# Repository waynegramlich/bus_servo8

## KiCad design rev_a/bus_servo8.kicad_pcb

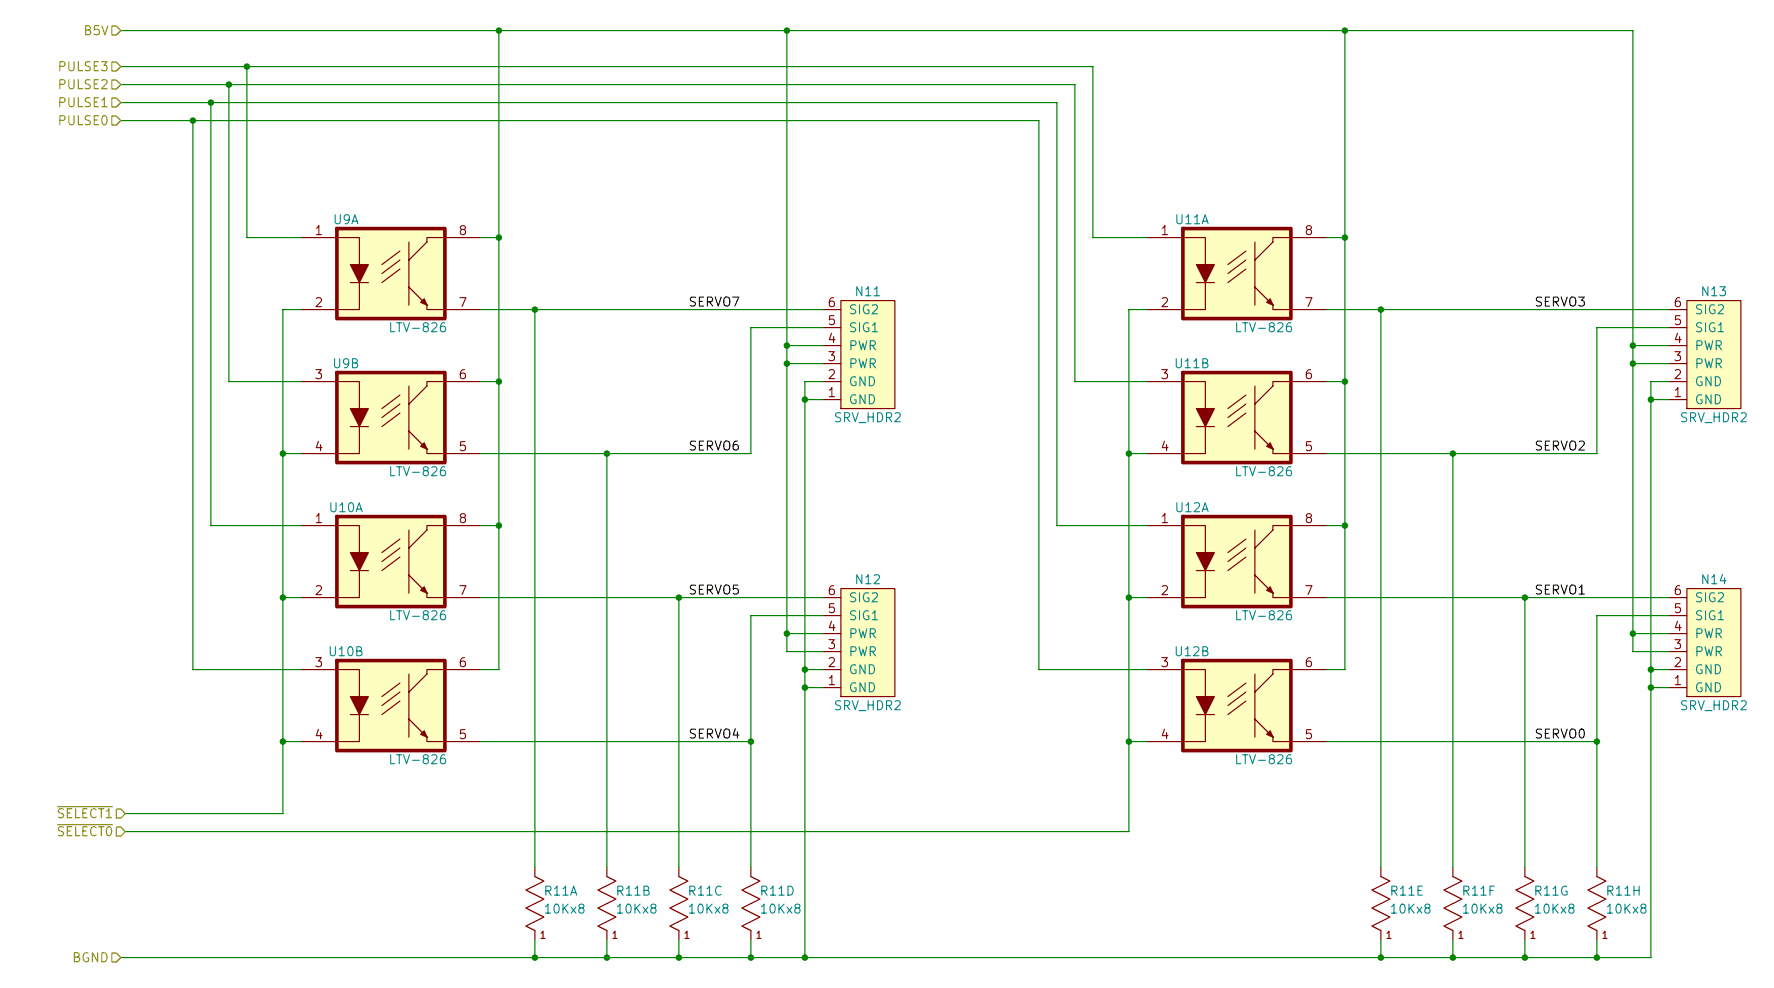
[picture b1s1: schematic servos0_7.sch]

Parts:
N11, N12, N13, N14: SRV_HDR2; Pin_Header_Straight_2x03
R11: 10Kx8; Pin_Header_Straight_1x09
U9, U10, U11, U12: LTV-826; DIP-8__300

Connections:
/Processor/B5V: N11.3 (PWR), N11.4 (PWR), N12.3 (PWR), N12.4 (PWR), N13.3 (PWR), N13.4 (PWR), N14.3 (PWR), N14.4 (PWR), U9.6, U9.8, U10.6, U10.8, U11.6, U11.8, U12.6, U12.8; also elsewhere on the board
/Processor/BGND: N11.1 (GND), N11.2 (GND), N12.1 (GND), N12.2 (GND), N13.1 (GND), N13.2 (GND), N14.1 (GND), N14.2 (GND), R11.1; also elsewhere on the board
/Processor/PULSE0: U10.3, U12.3; also elsewhere on the board
/Processor/PULSE1: U10.1, U12.1; also elsewhere on the board
/Processor/PULSE2: U9.3, U11.3; also elsewhere on the board
/Processor/PULSE3: U9.1, U11.1; also elsewhere on the board
/Processor/~SELECT0: U11.2, U11.4, U12.2, U12.4; also elsewhere on the board
/Processor/~SELECT1: U9.2, U9.4, U10.2, U10.4; also elsewhere on the board
/Servos_0:7/SERVO0: N14.5 (SIG1), R11.9, U12.5
/Servos_0:7/SERVO1: N14.6 (SIG2), R11.8, U12.7
/Servos_0:7/SERVO2: N13.5 (SIG1), R11.7, U11.5
/Servos_0:7/SERVO3: N13.6 (SIG2), R11.6, U11.7
/Servos_0:7/SERVO4: N12.5 (SIG1), R11.5, U10.5
/Servos_0:7/SERVO5: N12.6 (SIG2), R11.4, U10.7
/Servos_0:7/SERVO6: N11.5 (SIG1), R11.3, U9.5
/Servos_0:7/SERVO7: N11.6 (SIG2), R11.2, U9.7

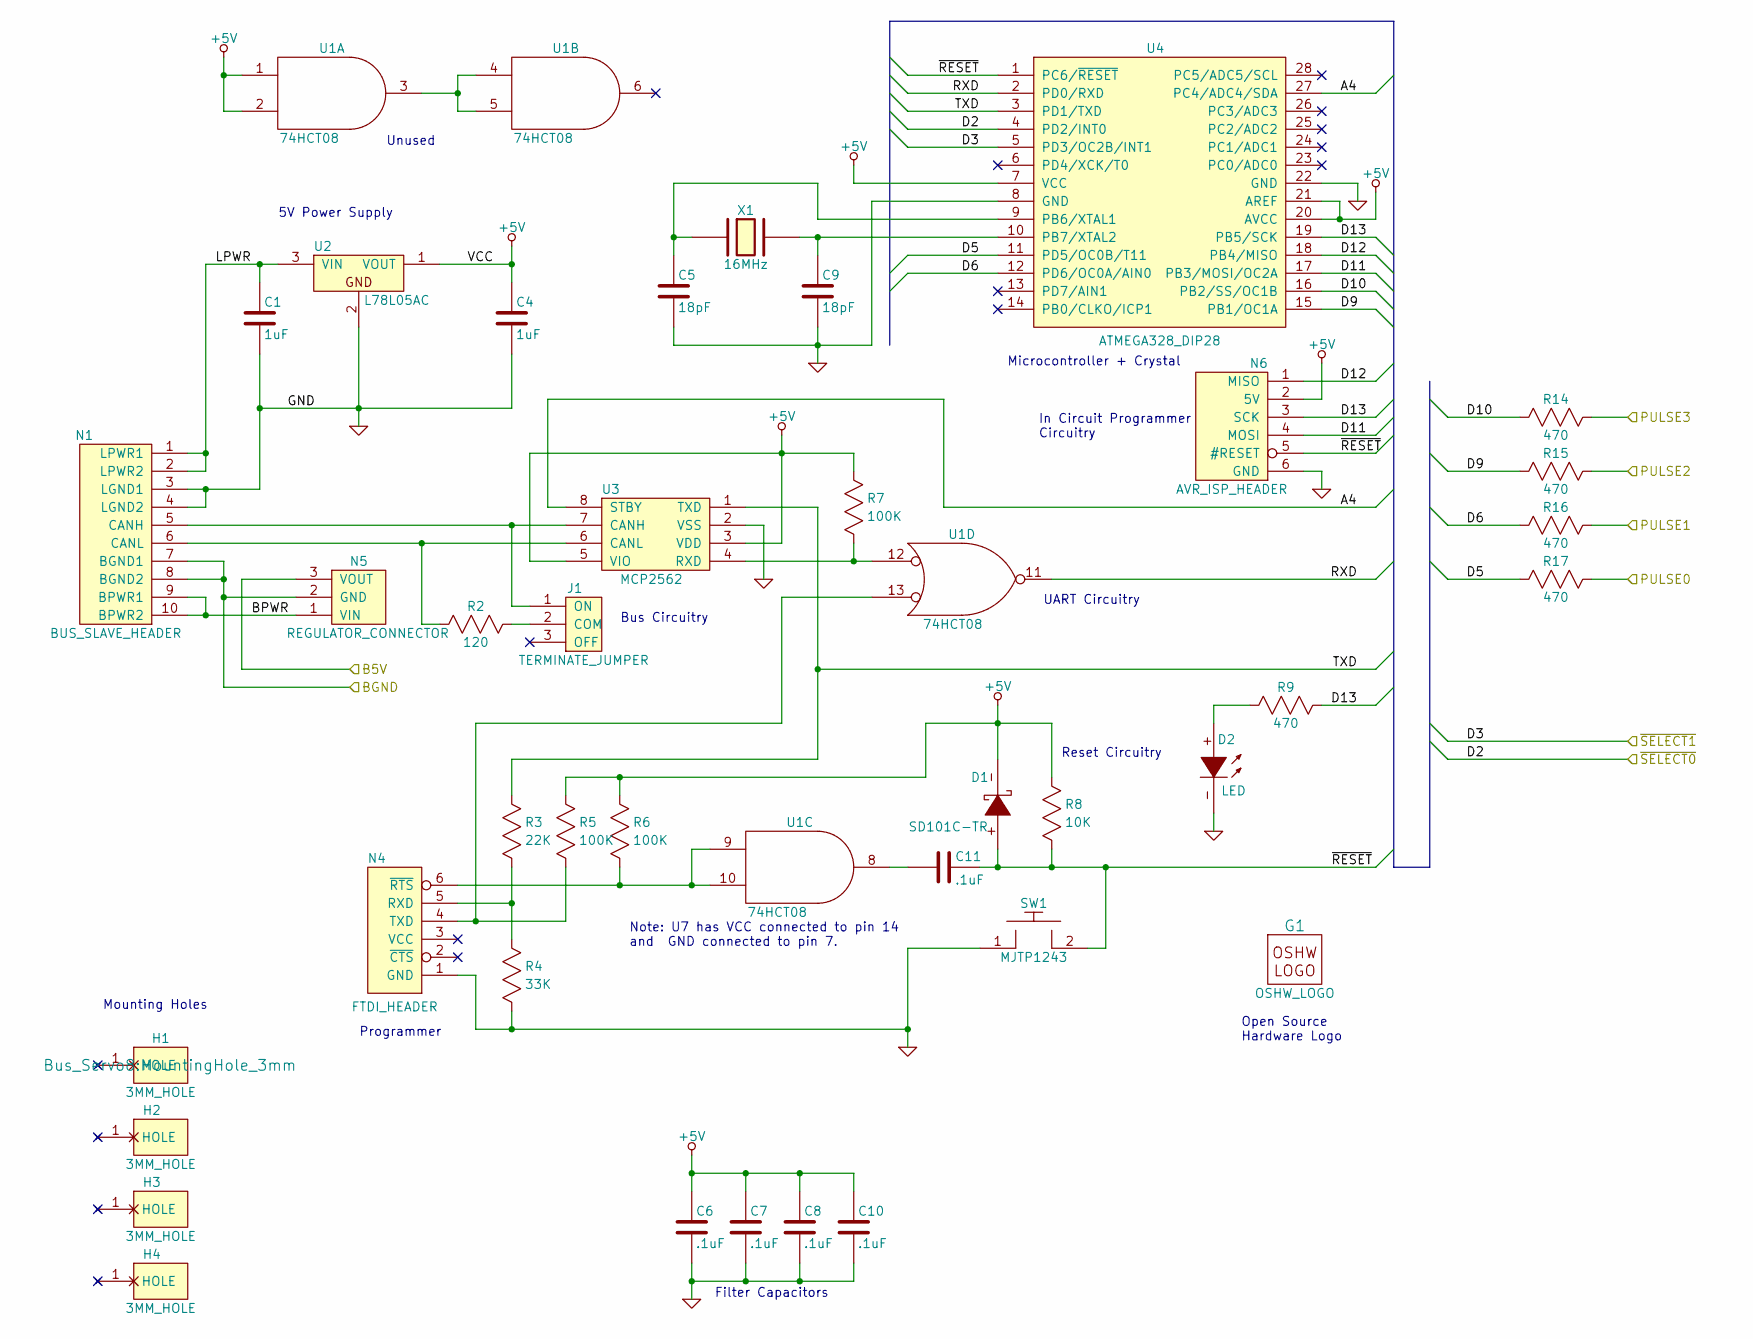
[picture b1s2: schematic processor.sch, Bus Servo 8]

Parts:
C1, C4: 1uF; Capacitor3MMDiscRM2.5
C5, C9: 18pF; Capacitor4x3RM2-5_RevB
C6, C7, C8, C10, C11: .1uF; Capacitor4x3RM2-5_RevB
D1: SD101C-TR; Diode_DO-41_SOD81_Horizontal_RM10
D2: LED; T1_LED
G1: OSHW_LOGO; OSHW_LOGO_300mil
H1, H2, H3, H4: 3MM_HOLE; MountingHole_3mm
J1: TERMINATE_JUMPER; Pin_Header_Straight_1x03
N1: BUS_SLAVE_HEADER; Pin_Header_Straight_2x05_Shrouded
N4: FTDI_HEADER; Pin_Header_Straight_1x06
N5: REGULATOR_CONNECTOR; OKI_DC_TO_DC_CONNECTOR
N6: AVR_ISP_HEADER; Pin_Header_Straight_2x03
R2: 120; Resistor_Horizontal_400
R3: 22K; Resistor_Horizontal_400
R4: 33K; Resistor_Horizontal_400
R5, R6, R7: 100K; Resistor_Horizontal_400
R8: 10K; Resistor_Horizontal_400
R9, R14, R15, R16, R17: 470; Resistor_Horizontal_400
SW1: MJTP1243; Button_6.5MM
U1: 74HCT08; DIP-14__300
U2: L78L05AC; TO92_123
U3: MCP2562; DIP-8__300
U4: ATMEGA328_DIP28; DIP-28__300
X1: 16MHz; Crystal_HC49-U_Vertical

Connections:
+5V: C4.1, C6.1, C7.1, C8.1, C10.1, D1.-, N6.2 (5V), R5.2, R6.2, R7.2, R8.2, U1.1, U1.2, U1.14 (VCC), U2.1 (VOUT), U3.3 (VDD), U3.5 (VIO), U4.7 (VCC), U4.20 (AVCC), U4.21 (AREF)
/Processor/A4: U3.8 (STBY), U4.27 (PC4/ADC4/SDA)
/Processor/B5V: N5.3 (VOUT); also elsewhere on the board
/Processor/BGND: N1.7 (BGND1), N1.8 (BGND2), N5.2 (GND); also elsewhere on the board
/Processor/BPWR: N1.9 (BPWR1), N1.10 (BPWR2), N5.1 (VIN)
/Processor/D5: R17.1, U4.11 (PD5/OC0B/T11)
/Processor/D6: R16.1, U4.12 (PD6/OC0A/AIN0)
/Processor/D9: R15.1, U4.15 (PB1/OC1A)
/Processor/D10: R14.1, U4.16 (PB2/SS/OC1B)
/Processor/D11: N6.4 (MOSI), U4.17 (PB3/MOSI/OC2A)
/Processor/D12: N6.1 (MISO), U4.18 (PB4/MISO)
/Processor/D13: N6.3 (SCK), R9.2, U4.19 (PB5/SCK)
/Processor/LPWR: C1.1, N1.1 (LPWR1), N1.2 (LPWR2), U2.3 (VIN)
/Processor/PULSE0: R17.2; also elsewhere on the board
/Processor/PULSE1: R16.2; also elsewhere on the board
/Processor/PULSE2: R15.2; also elsewhere on the board
/Processor/PULSE3: R14.2; also elsewhere on the board
/Processor/RXD: U1.11, U4.2 (PD0/RXD)
/Processor/TXD: R3.2, U3.1 (TXD), U4.3 (PD1/TXD)
/Processor/~RESET: C11.2, D1.+, N6.5 (#RESET), R8.1, SW1.2, U4.1 (PC6/~RESET)
/Processor/~SELECT0: U4.4 (PD2/INT0); also elsewhere on the board
/Processor/~SELECT1: U4.5 (PD3/OC2B/INT1); also elsewhere on the board
GND: C1.2, C4.2, C5.2, C6.2, C7.2, C8.2, C9.2, C10.2, D2.-, N1.3 (LGND1), N1.4 (LGND2), N4.1 (GND), N6.6 (GND), R4.1, SW1.1, U1.7 (GND), U2.2, U3.2 (VSS), U4.8 (GND), U4.22 (GND)
unnamed: C5.1, U4.9 (PB6/XTAL1), X1.1
unnamed: C9.1, U4.10 (PB7/XTAL2), X1.2
unnamed: C11.1, U1.8
unnamed: D2.+, R9.1
unnamed: J1.1 (ON), N1.5 (CANH), U3.7 (CANH)
unnamed: J1.2 (COM), R2.2
unnamed: N1.6 (CANL), R2.1, U3.6 (CANL)
unnamed: N4.4 (TXD), R5.1, U1.13
unnamed: N4.5 (RXD), R3.1, R4.2
unnamed: N4.6 (~RTS), R6.1, U1.9, U1.10
unnamed: R7.1, U1.12, U3.4 (RXD)
unnamed: U1.3, U1.4, U1.5

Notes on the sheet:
Filter Capacitors
Reset Circuitry
Programmer
UART Circuitry
5V Power Supply
Unused
Note: U7 has VCC connected to pin 14 and GND connected to pin 7.
In Circuit Programmer Circuitry
Bus Circuitry
Mounting Holes
Open Source Hardware Logo
Microcontroller + Crystal

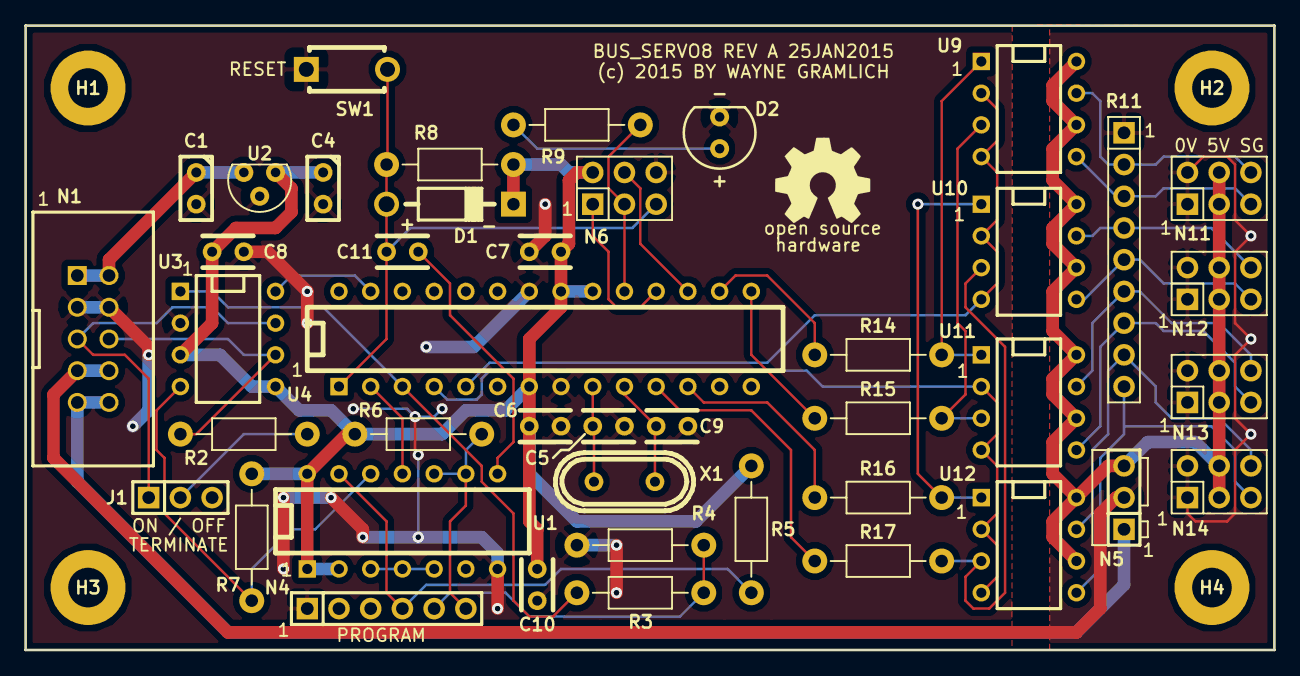
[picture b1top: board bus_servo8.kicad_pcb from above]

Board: 2 copper layers, 100.0 x 50.0 mm, 48 parts (0 on the bottom side), 43 nets.

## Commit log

2015-01-25 bus_servo8 rev. A is ready.
2015-01-27 Changed mounting holes to be masked.

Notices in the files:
rev_a/bus_servo8.kicad_pcb:
(c) 2015 BY WAYNE GRAMLICH
